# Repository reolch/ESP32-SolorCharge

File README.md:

# ESP32-SolorCharge
Esp32を太陽光発電とスーパーキャパシターで駆動させる試みです。

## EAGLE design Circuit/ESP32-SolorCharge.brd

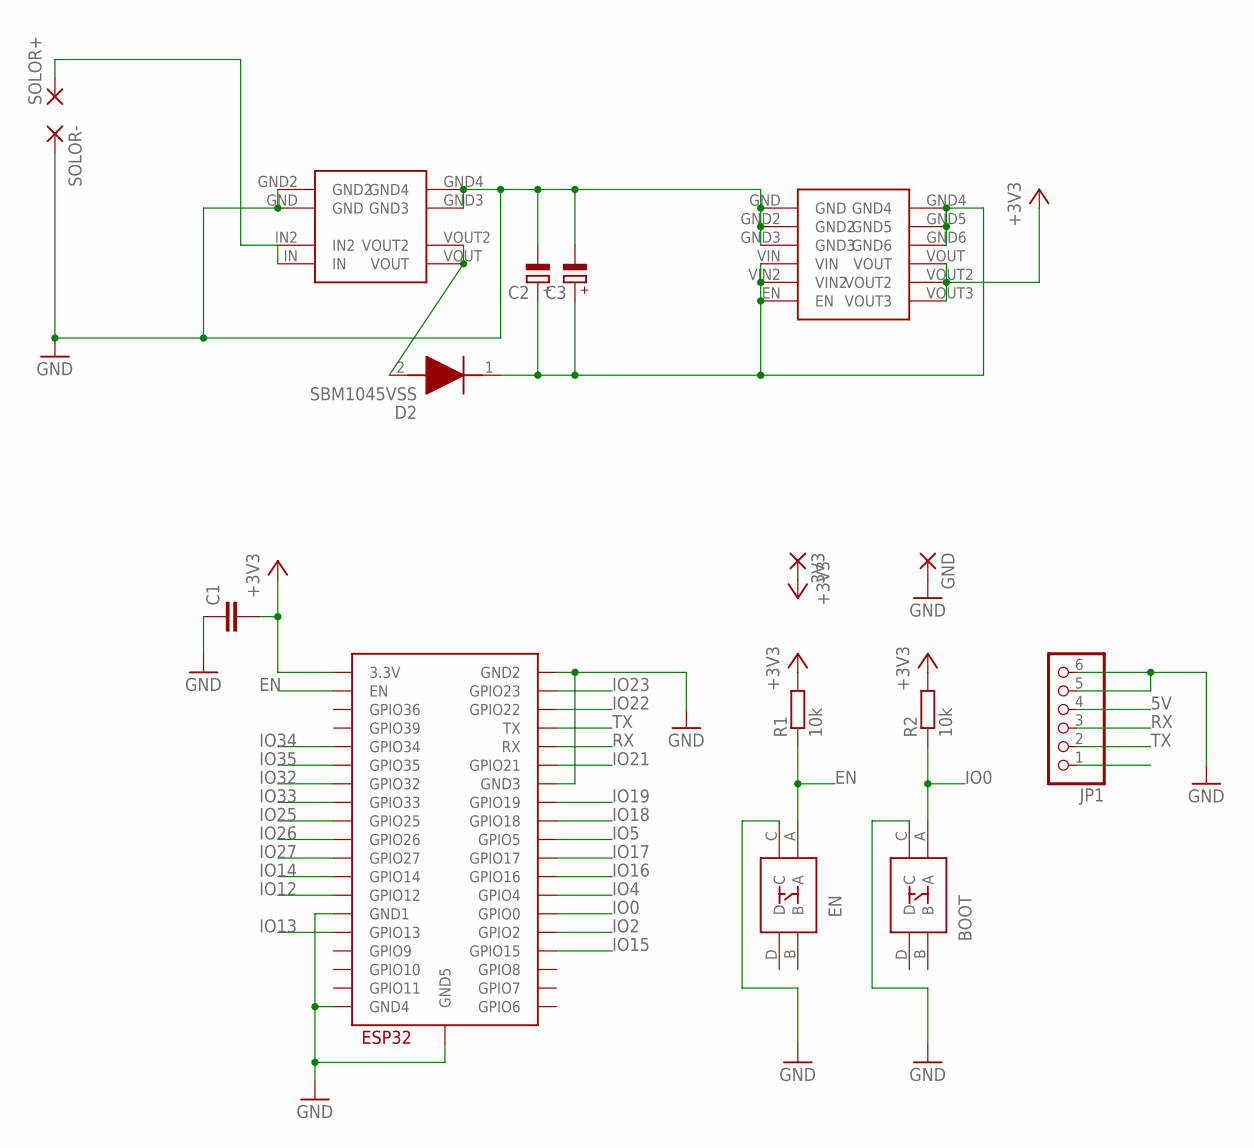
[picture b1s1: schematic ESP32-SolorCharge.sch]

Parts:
3V3: 2,54/1,0
BOOT: TS-06104; TS06104
C1: C-EU025-025X050; C025-025X050
C2, C3: CPOL-EUE7.5-16; E7,5-16
D2: SBM1045VSS; DIOAD2855W130L835D505
EN: TS-06104; TS06104
GND: 2,54/1,0
JP1: PINHD-1X6; 1X06
R1, R2: 10k; R0603
SOLOR+: 2,54/1,0
SOLOR-: 2,54/1,0
U$1: ESP32-WROOM
U$2: TPS63070
U$3: TPS63020

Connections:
5V: JP1.4
+3V3: 3V3.1, C1.2, R1.2, R2.2, U$1.3V3 (3.3V), U$3.VOUT, U$3.VOUT2, U$3.VOUT3
EN: EN.A, R1.1, U$1.EN
GND: BOOT.C, C1.1, C2.-, C3.-, EN.C, GND.1, JP1.5, JP1.6, SOLOR-.1, U$1.GND1, U$1.GND2, U$1.GND3, U$1.GND4, U$1.GND5, U$2.GND, U$2.GND2, U$2.GND3, U$2.GND4, U$3.GND, U$3.GND2, U$3.GND3
IO0: BOOT.A, R2.1, U$1.IO0 (GPIO0)
IO2: U$1.IO2 (GPIO2)
IO4: U$1.IO4 (GPIO4)
IO5: U$1.IO5 (GPIO5)
IO12: U$1.IO12 (GPIO12)
IO13: U$1.IO13 (GPIO13)
IO14: U$1.IO14 (GPIO14)
IO15: U$1.IO15 (GPIO15)
IO16: U$1.IO16 (GPIO16)
IO17: U$1.IO17 (GPIO17)
IO18: U$1.IO18 (GPIO18)
IO19: U$1.IO19 (GPIO19)
IO21: U$1.IO21 (GPIO21)
IO22: U$1.IO22 (GPIO22)
IO23: U$1.IO23 (GPIO23)
IO25: U$1.IO25 (GPIO25)
IO26: U$1.IO26 (GPIO26)
IO27: U$1.IO27 (GPIO27)
IO32: U$1.IO32 (GPIO32)
IO33: U$1.IO33 (GPIO33)
IO34: U$1.IO34 (GPIO34)
IO35: U$1.IO35 (GPIO35)
unnamed: D2.2 (A), U$2.VOUT, U$2.VOUT2
unnamed: C2.+, C3.+, D2.1 (K), U$3.EN, U$3.GND4, U$3.GND5, U$3.GND6, U$3.VIN, U$3.VIN2
unnamed: SOLOR+.1, U$2.IN, U$2.IN2
RX: JP1.3, U$1.RX
TX: JP1.2, U$1.TX

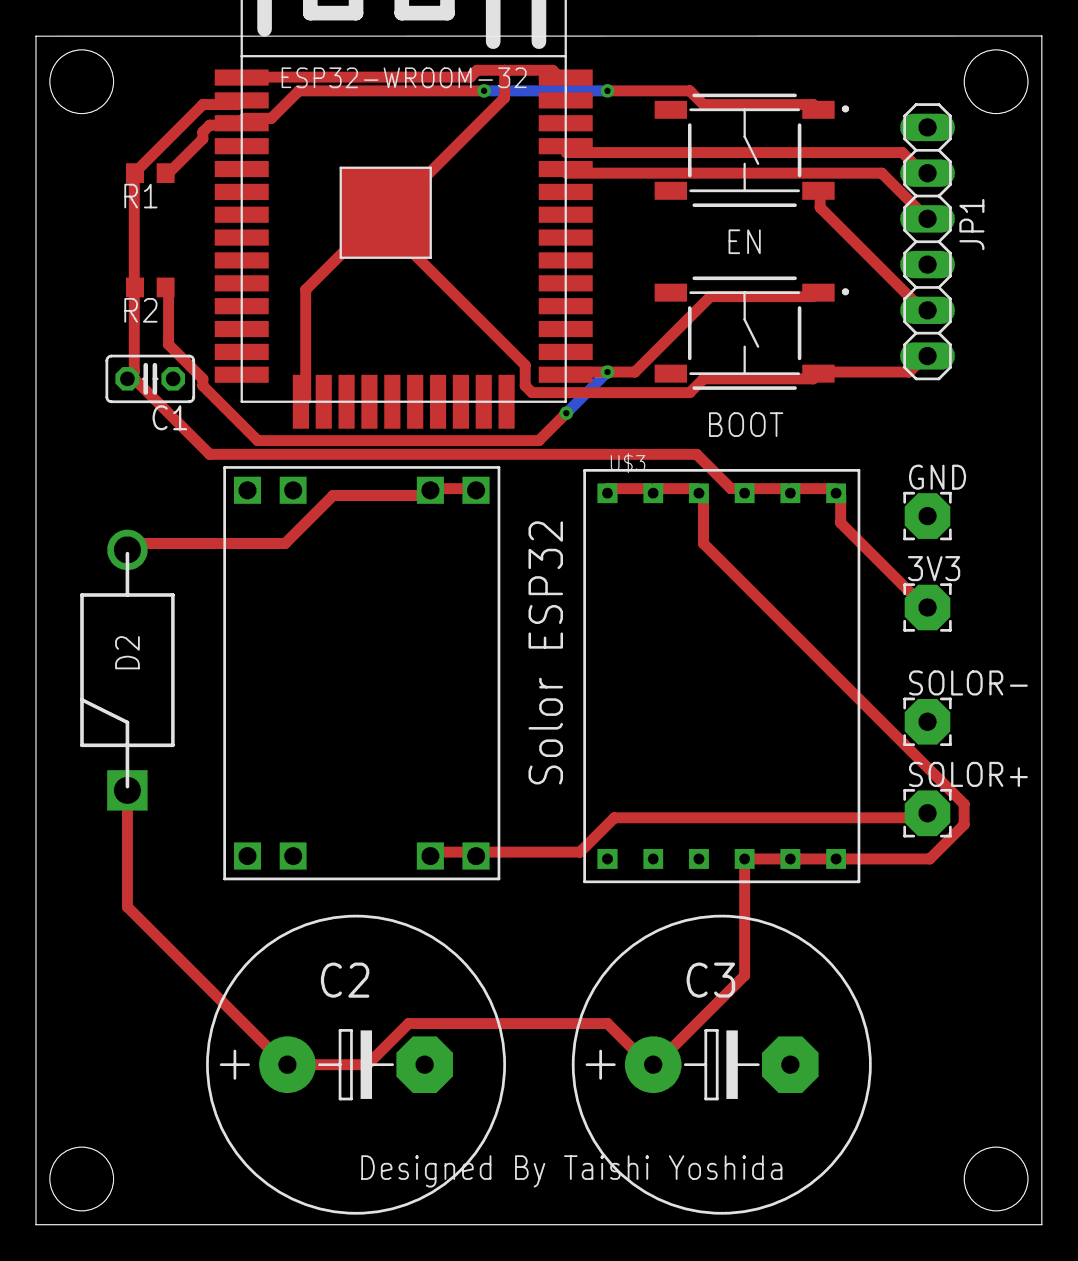
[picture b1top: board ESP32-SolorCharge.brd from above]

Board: 2 copper layers, 55.9 x 66.0 mm, 16 parts (0 on the bottom side), 9 nets.

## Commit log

2022-11-21 現在の進捗をPushします。
2022-11-21 使用中のライブラリを追加しました。
